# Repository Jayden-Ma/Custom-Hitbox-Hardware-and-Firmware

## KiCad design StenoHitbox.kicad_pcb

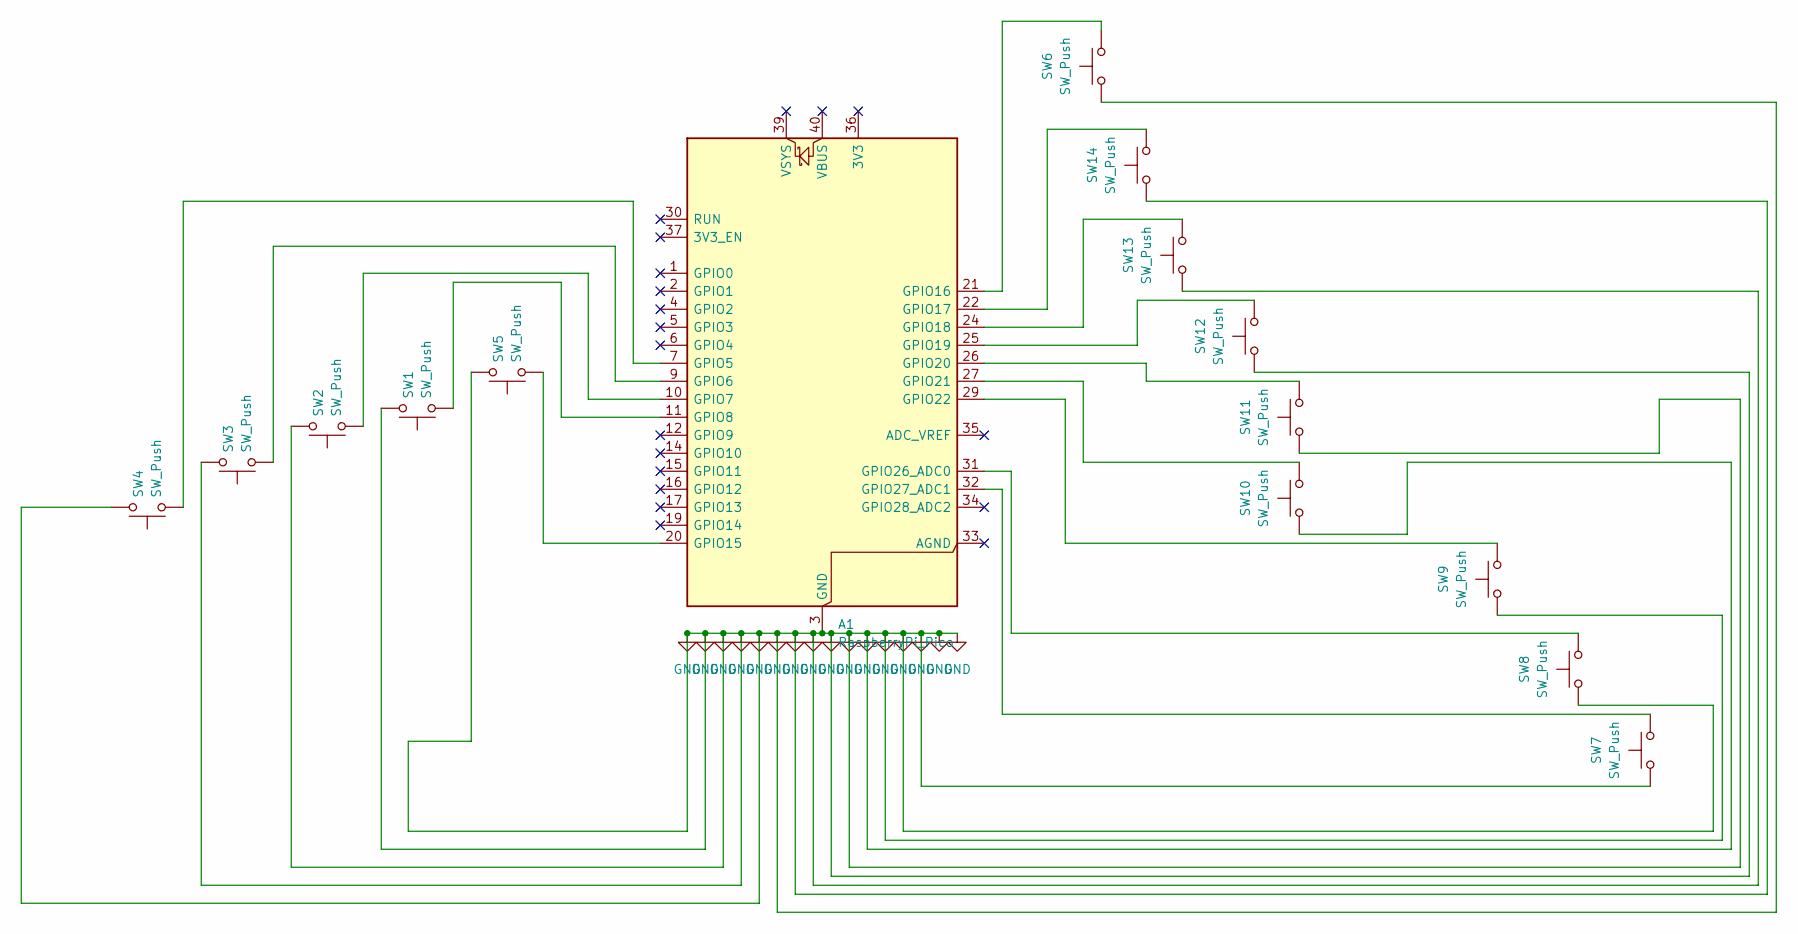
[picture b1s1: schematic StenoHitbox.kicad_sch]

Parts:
A1: RaspberryPi_Pico; RaspberryPi_Pico_Common_Unspecified
SW1, SW2, SW3, SW4, SW5, SW6, SW7, SW8, SW9, SW10, SW11, SW12, SW13, SW14: SW_Push; SW_Hotswap_Kailh_Choc_V1V2

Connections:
GND: A1.3 (GND), A1.8 (GND), A1.13 (GND), A1.18 (GND), A1.23 (GND), A1.28 (GND), A1.38 (GND), SW1.2, SW2.2, SW3.2, SW4.2, SW5.2, SW6.1, SW7.1, SW8.1, SW9.1, SW10.1, SW11.1, SW12.1, SW13.1, SW14.1
unnamed: A1.7 (GPIO5), SW4.1
unnamed: A1.9 (GPIO6), SW3.1
unnamed: A1.10 (GPIO7), SW2.1
unnamed: A1.11 (GPIO8), SW1.1
unnamed: A1.20 (GPIO15), SW5.1
unnamed: A1.21 (GPIO16), SW6.2
unnamed: A1.22 (GPIO17), SW14.2
unnamed: A1.24 (GPIO18), SW13.2
unnamed: A1.25 (GPIO19), SW12.2
unnamed: A1.26 (GPIO20), SW11.2
unnamed: A1.27 (GPIO21), SW10.2
unnamed: A1.29 (GPIO22), SW9.2
unnamed: A1.31 (GPIO26_ADC0), SW8.2
unnamed: A1.32 (GPIO27_ADC1), SW7.2

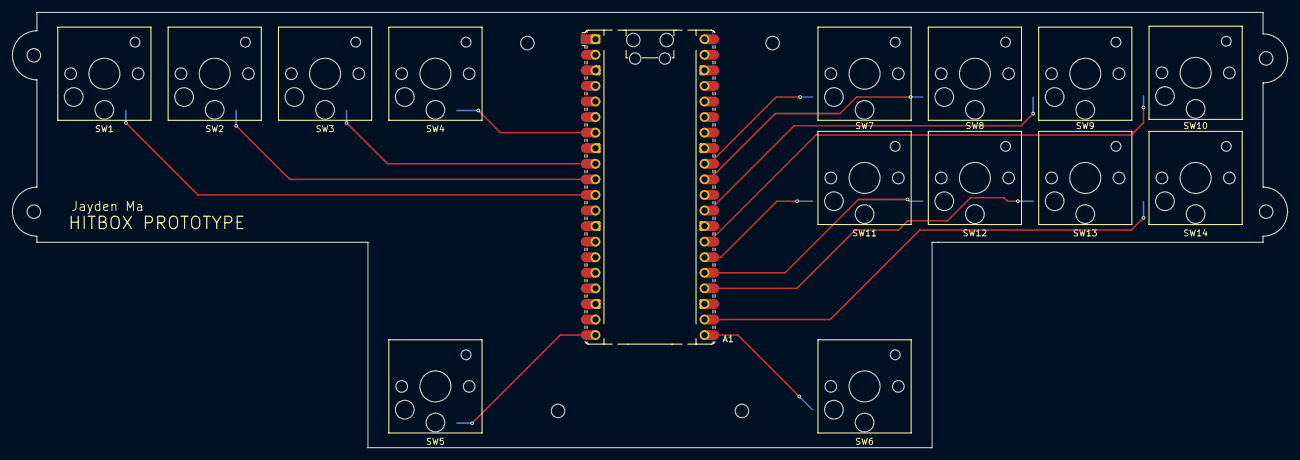
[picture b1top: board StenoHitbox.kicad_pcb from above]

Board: 2 copper layers, 208.0 x 71.0 mm, 15 parts (0 on the bottom side), 15 nets.
